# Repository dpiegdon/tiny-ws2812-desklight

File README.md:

<!-- vim: fo=a tw=80 colorcolumn=80 syntax=markdown :
-->

ATTiny10-powered WS2812 desklight
=================================

Controller firmware and hardware for a very simple desklight that has a button
and a digital encoder for color/brightness selection.

Controls a strip of WS2812 RGB LEDs which could e.g. be mounted at the bottom
edge of your desktop monitor facing down towards the desk surface.

![PCB v1.0 bottom side photo](
https://github.com/dpiegdon/tiny-ws2812-desklight/blob/master/hardware/production/tiny-ws2812-desklight-v1.0_bottom-pcb.jpg?raw=true)

(Above: bottom side of v1.0 PCB)

Authors
-------

David R. Piegdon <dgit@piegdon.de>

License
-------

All files in this repository are released unter the GNU General Public License
Version 3 or later. This includes the schematic, the routed PCB and the firmware
as well as the documentation and accompanying materials. See the file COPYING
for more information.

Device interface
================

The rotary encoder has a button and can be rotated in both directions. The
button cycles through different modes. In each mode you change a different
variable by rotating the encoder:

* Mode 1: change brightness

* Mode 2: change color

* Mode 3: change number of enabled LEDs

* Mode 4: change starting position of enabled LEDs

Pressing the button for more than half a second resets all values to their
defaults.

Firmware
========

You probably have to use a recent AVR-GCC Version for compilation. Version 5.4.0
is good, 7.3.0 yields even better results. As the ATTiny10 is very
space-constrained, older gcc versions may not optimize well enough to meet the
space-constrains with the current feature set.

If you want to change the number of lights in the firmware, please do so in
`ws2812.h`. If you know what you are doing, you can also change the assignment
to `light_count` in the firmware files (in `ws2812_init()`, `calca_init()`, if
you don't want to recompile.)

Note that with the current <b>master</b> branch firmware you can use up to 126
LEDs. The actual constraint is something like `lightcount <=
max_value(int8_t)-1`.

Firmware Changelog
------------------

### v1.0

Supports four modes (brightness/color/enable-count/start-pos),
should support 63 LEDs. Required GCC 7.3.0 or similar to fit
size-constraints.

### v1.1

Improved binary size. Now supports building with GCC 5.4.0.

### v1.2

Support up to 126 LEDs.

### v1.3

Fixed rotary dial directions to be consistent across modes.

### v1.4

Fixed WS2812 timings to properly work with all LEDs. Allow `LIGHT_COUNT` to be
overriden via `CXXFLAGS`.

### master

(no more changes)

Hardware
========

You can find a Kicad-based schematic in the hardware directory.

The firmware is written for an Atmel ATTiny10. The latest version does not use
the ADC anymore, so an ATTiny9 should do fine, too.

Connect a 5V 1500mA (or better 2000mA) power supply for a strip with 34 LEDs.

Hardware Errata
---------------

### v1.0

Version 1.0 of hardware is <i>fully functional and works perfectly fine</i>.
However, a few changes might be useful when doing another revision:

 * Schematic: Remove comment on questionable 1K resistor value. 1K resistors
   between uC and encoder are ok. Comment in schematic was already removed
   shortly after tag v1.0, as already can be seen in released PDF schematic of
   v1.0.

 * Schematic/BOM: Create a BOM. Well, maybe just specify the kind of rotary
   encoder. (Look for <i>EC11 digital encoder</i> on your favourite cheap
   chinese parts supplier)

 * PCB: Increase drill size for power lines on P2 and P3, so power cables can
   be soldered directly to PCB easily.

 * PCB: Mark RESET pin of TPI so it can be found easily when re-flashing a uC.

 * PCB: Mark TPI interface as "TPI".

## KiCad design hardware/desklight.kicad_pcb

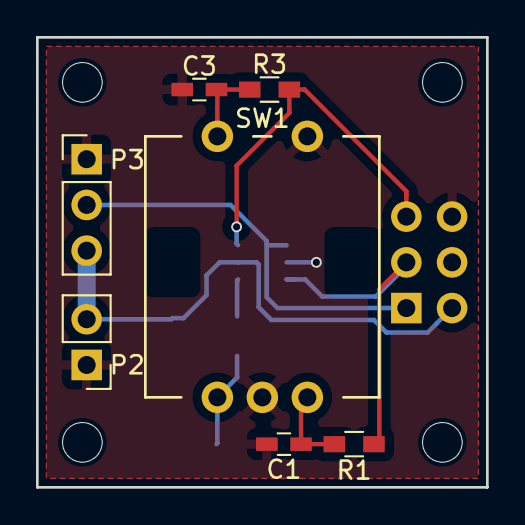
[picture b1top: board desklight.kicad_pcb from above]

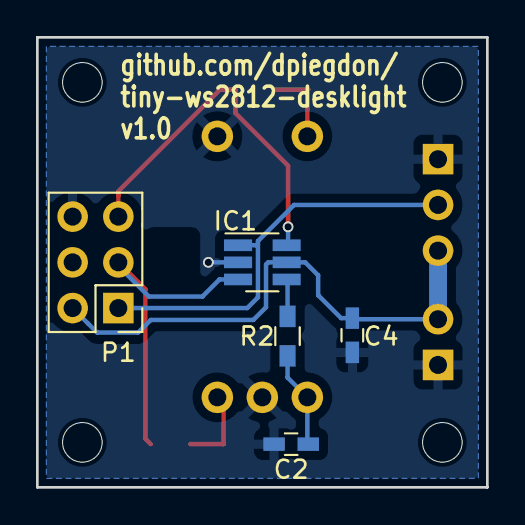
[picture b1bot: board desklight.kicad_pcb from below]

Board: 2 copper layers, 25.0 x 25.0 mm, 12 parts (5 on the bottom side), 9 nets.

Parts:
C1, C2, C3: C; C_0603_HandSoldering
C4: 100n; C_0603_HandSoldering
IC1: ATTINY10-TS; SOT-23-6_Handsoldering
P1: AVR_TPI; Pin_Header_Straight_2x03_Pitch2.54mm
P2: Pwr5V1500mA; Pin_Header_Straight_1x02_Pitch2.54mm
P3: WS2812_CON; Pin_Header_Straight_1x03_Pitch2.54mm
R1, R2, R3: 1k; R_0603_HandSoldering
SW1: Rotary_Encoder_Switch; Encoder_PEC11R

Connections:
/DOUT: IC1.1, P1.1, P3.2
/SCK: IC1.3, P1.3, R1.1
/~RESET: IC1.6, P1.5, R3.1
GND: C1.2, C2.2, C3.2, C4.2, IC1.2, P1.6, P2.1, P3.1, SW1.2, SW1.5
unnamed: C1.1, R1.2, SW1.3
unnamed: C2.1, R2.2, SW1.1
unnamed: C3.1, R3.2, SW1.4
unnamed: IC1.4, R2.1
VCC: C4.1, IC1.5, P1.2, P2.2, P3.3

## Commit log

2017-01-24 initial, dumb version of desklamp
2017-01-25 sweep, preps for switch and potentiometer
2017-01-25 fixed color choosing
2017-01-27 preps to use ADC for potentiometer
2017-01-27 simple attenuation/brightness via potentiometer.
2017-01-27 license and readme
2017-01-27 swap pins for switch and potentiometer to allow power-reduced setup
2017-01-27 increased sweep strength during startup
2017-01-27 fixed sweep code to make sure first LED really has the selected color
2017-01-27 use INT0 for switch, deeper sleep mode
2017-01-28 clock down for powersaving; only update if actual r/g/b values change.
2017-01-28 improve channel brightness linearity and reduce flickering at cost of clocking speed
2017-01-28 added schematic, directory layout refactored
2017-01-28 notes
2017-01-29 reduce flickering: hardware improvement, IIR filter for ADC; use more dynamic of potentiometer
2017-01-29 ignore more stuff
2017-01-29 README: updated notes on hardware
2017-01-31 disable unneeded Timer0; readme: ideas
2017-02-01 disable unneeded digital inputs
2017-02-01 cleanup/reduction
2017-02-01 generate stackusage files during compilation
2017-02-01 clean generated su files
2017-03-17 initial refactor and preps for encoder use
2017-03-18 refactor/changes for rotary encoder
2017-03-18 more cleanup/refactor
2017-03-18 less in ISR, more in main to recude required stackuse
2017-03-20 fixed multiple bugs, verified function
2017-03-20 update only when settings actually changed
2017-03-20 fixed error in bitfield use
2017-03-20 set fuses to disable RESET, better color spacing, reset settings after long-press
2017-03-20 default to red
2017-03-20 WIP: make sure there can be no stackoverflow; memory cleanup
2017-03-20 WIP: more reduction of ISR; responsiveness should not be an issue
2017-03-20 schematic cleanup
2017-03-20 notes. firmware is fine.
2017-03-22 basic pcb design
2017-06-27 keywords in docs
2017-07-14 support selecting a window of LEDs to light up
2017-08-26 add debouncing caps
2018-06-19 re-routed with cleanup
2018-06-19 re-route in 2.5x2.5cm formfactor.
2018-06-19 added resistors to allow in-circuit programming
2018-06-19 PCB version 1.0, also panelized in 10x10cm and production-ready zip file for upload to your favourite PCB store.
2018-06-19 switch firmware to c++17
2018-06-19 code reduction and cleanup
2018-06-20 more code cleanup and size reductions
2018-06-20 further firmware refactor
2018-06-21 Makefile cleanup to properly represent switch to c++
2018-06-21 cleanup
2018-06-22 fix some logic errors
2018-06-22 fix further bugs
2018-06-25 Makefile options for better assembler output
2018-06-25 fix bug where (non-existing) .rodata section was used for data. never use static data on attiny10...
2018-06-26 also fix static-const vars that were optimized out as constants.
2018-06-26 allow cyclic wraparound for spot
2018-06-26 make light_count variable so it can be changed in bin-file.
2018-06-26 firmware release v1.0, readme
2018-06-26 build for local releases
2018-06-26 signed/unsigned cleanup reduces binary size a lot
2018-06-26 reduce multiplication and division to shifts to further reduce binary size
2018-06-26 firmware release 1.1, readme
2018-07-02 further minimization, makefile cleanup
2018-07-02 fix typo errors
2018-07-07 schematic: 1K resistors seem fine
2018-07-07 doc: photo
2018-07-07 added PDF of schematic
2018-07-09 support up to 126 LEDs
2018-07-09 errata/README updates
2018-07-09 test-code for 126 LEDs
2018-07-09 firmware release v1.2
2018-07-10 support usbasp programmer besides avrispmkII, don't override user choice.
2018-07-25 fix rotary interface such that meaning is same for all modes
2018-07-25 firmware release v1.3
2018-07-26 improve WS2812 timings to work with all lights and be consistent (same length for both 0 and 1)
2018-07-26 light_count: move to calca and define such that CXXFLAGS can override it
2018-07-26 firmware-release v1.4
2018-10-28 ws2812 header: generalize, so integration on other processors is easier
2025-09-13 forward-port PCB to current kicad, include EC11 step model
2025-09-13 basic enclosure model
